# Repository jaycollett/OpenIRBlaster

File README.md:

# OpenIRBlaster

An open-source IR receiver and transmitter for Home Assistant. Custom PCB, 3D-printed case, ESPHome firmware, about $22 to $25 in parts.

[![GitHub Release][releases-shield]][releases]
[![License][license-shield]](LICENSE)
[![hacs][hacsbadge]][hacs]

📖 **[Read the full story and build guide on my blog](https://www.jaycollett.com/2026/02/openirblaster-finally-truly-simple-ir-control-for-home-assistant/)**

## The integration is deprecated. The hardware is not.

Home Assistant 2026.4 added a built-in `infrared` entity platform, and [HAIR](https://github.com/DAB-LABS/HAIR) builds a full IR code manager on top of it: a live signal sniffer, protocol decoding, climate state matrices, and import from SmartIR, Flipper Zero, LIRC and Girr. It does everything this integration does and a great deal more, and it is in the HACS default store.

So this integration is winding down. It still works, it is not going to break tomorrow, and nothing is being deleted in this release. It will not gain new features.

The hardware is unaffected and is where this project continues. OpenIRBlaster is a board, a case, a bill of materials and a firmware image, none of which HAIR provides.

**If you are already using this integration:** move your codes across before you delete its storage file. From version 1.3.2, removing the integration leaves that file in place. Version 1.3.1 and earlier deleted it along with the integration, so on those versions update or move your codes first. Your stored codes hold the carrier frequency measured when each was learned, and the new infrared platform does not report one, so anything re-learned later comes back at the 38 kHz default. See [Moving your codes to HAIR](#moving-your-codes-to-hair). Nothing is deleted and your setup keeps working while you check the result.

**If you are new here:** build the hardware, flash it, and use it with HAIR.

## What it is

A dedicated ESP8266 board built around IR, rather than a general-purpose dev board with an LED soldered on.

Transistor-driven IR LEDs (eight of them, 39 ohm limiting resistors, IRLML6344 MOSFET) give strong output and 360 degree coverage, so it works across a room rather than only when pointed at the target. A TSOP38238 receiver handles learning. The ESPHome firmware ships with `dashboard_import`, so the ESPHome dashboard can adopt the device with one click.

Everything needed to build one is in [`hardware/`](hardware/): schematic and board layout, the bill of materials, STLs for the case, the firmware source and a prebuilt binary.

## Requirements

- Home Assistant 2024.12 or newer for this integration.
- For HAIR, check its own requirements. Native IR capture and plucking need Home Assistant 2026.6 or newer, because that is the release where the infrared receiver API landed. 2026.9 or newer is the safer floor.
- An OpenIRBlaster board, or other ESPHome hardware with an IR receiver and transmitter.

See the [Hardware Overview](docs/hardware-overview.md) for the build.

## Moving your codes to HAIR

### Do this before you delete anything

Every code you learned here carries the carrier frequency measured when it was captured. Home Assistant's infrared platform does not report a carrier, so a code you learn again afterwards comes back at the 38 kHz default.

Most remotes are 38 kHz and would not notice. A device running at 36 or 40 kHz would, and for those the difference is the code working or not working. That measured value exists in one place only, this integration's storage file, and re-learning cannot bring it back.

Both routes below preserve it. Take one of them before you delete `.storage/openirblaster_<entry_id>`.

From version 1.3.2, removing the integration in Home Assistant keeps that file, so your codes are still on disk afterwards and the command-line export below can convert them. Version 1.3.1 and earlier deleted the file when you deleted the integration entry, so if you are on one of those versions, update or export first.

If you remove a blaster and add it again, Home Assistant gives it a new entry ID and a new, empty storage file. The old file stays next to it with your codes in it. Once those codes are safely in HAIR you can delete the old file by hand.

### Pluck from HAIR (recommended)

HAIR pulls the codes out of this integration directly. No files to move, no remote to point at anything, and no infrared is broadcast while it happens.

1. Install HAIR from HACS and set it up.
2. Open HAIR, go to the **Plucker** tab, and add OpenIRBlaster as a blaster.
3. Pluck your codes by name.

This works because the integration implements HAIR's pluckable contract. See [Plucking codes into HAIR](docs/pluckable.md) for what that means and how it works.

### Export to a file

If you would rather move files yourself, or HAIR is not installed yet.

From the UI, while this integration is still installed:

1. Go to **Developer Tools** -> **Actions**.
2. Choose **OpenIRBlaster: Export codes to HAIR**.
3. Pick your device, and optionally choose how to split the codes into files.
4. Run it.

Files land in `hair/wigs/` in your Home Assistant config directory, which is where HAIR looks.

HAIR treats one file as one remote, so the **Split into** option matters if your library covers several devices. Splitting by tag or by the first word of each code name gives you one remote per device instead of one long list. You can re-split inside HAIR later either way.

From the command line, which also works after you have removed the integration (on 1.3.2 or later, where removal keeps the file):

```bash
python3 tools/openirblaster_to_wig.py ~/.homeassistant/.storage/openirblaster_<entry_id>
```

The file name has no extension, and there is one per blaster, so `ls ~/.homeassistant/.storage/openirblaster_*` shows you what to pass.

Run `--help` for output directory and grouping options. It needs nothing but Python 3.12 or newer and never writes to the file it reads. `custom_components/openirblaster/wig_export.py` is the whole implementation in one file with no imports from anything else, so you can copy that single file somewhere and run it if the repository is not handy.

### After moving

Check the codes work in HAIR before removing anything here. If a code did not convert, or carried tags or notes, the file export writes `openirblaster-export-receipt.txt` next to the wigs listing what was dropped and why. Tags and notes have no equivalent in HAIR's format, so they are reported rather than silently merged.

Keep your `.storage` file until you are satisfied. Removing the integration does not touch it, so when you no longer need it, delete it by hand.

## Installation

### HACS

1. Open HACS.
2. Click **Integrations**.
3. Click **+ Explore & Download Repositories**.
4. Search for "OpenIRBlaster".
5. Click **Download**.
6. Restart Home Assistant.
7. Go to **Settings** → **Devices & Services** → **Add Integration** and search for "OpenIRBlaster".

### Manual

1. Download the [latest release](https://github.com/jaycollett/OpenIRBlaster/releases).
2. Copy `custom_components/openirblaster` into your Home Assistant `custom_components` directory.
3. Restart Home Assistant.
4. Add the integration from **Settings** → **Devices & Services**.

## Using the integration

### Learn a code

1. Find the **Code Name** text field in your device's entity list.
2. Enter a name, for example "TV Power".
3. Press **Learn IR Code**.
4. Within 30 seconds, point your remote at the receiver and press the button.
5. A new button entity appears with that name.

### Manage codes

Rename by calling `openirblaster.rename_code` with the code's `id` and a `new_name`. The button updates immediately and its entity ID does not change, so automations keep working.

Delete from **Settings** → **Devices & Services** → **OpenIRBlaster** → **Configure** → **Manage IR Codes**. Deletion is always select-then-confirm.

Codes can also be saved, sent, renamed and deleted from scripts. See the [Home Assistant Integration](docs/home-assistant-integration.md) docs for the full service reference.

### Use in automations

```yaml
automation:
  - alias: "Turn off TV at bedtime"
    trigger:
      - platform: time
        at: "23:00:00"
    action:
      - service: button.press
        target:
          entity_id: button.openirblaster_tv_power
```

## Compatibility

The integration finds devices by ESPHome project name, looking for firmware that declares `project.name: "jaycollett.openirblaster"`. If you are building your own hardware, include that identifier in your ESPHome YAML or fork the integration.

### Third-party devices

Community members have run OpenIRBlaster on hardware it was not designed for. See [`docs/third-party-devices/`](docs/third-party-devices/):

- [Tuya IR Blasters](docs/third-party-devices/tuya-ir-blasters.md), covering S06, S18 and similar Tuya-branded repeaters

[PRs adding a guide are welcome](docs/third-party-devices/README.md#contributing-a-new-device-guide).

## Documentation

Full documentation lives in [`docs/`](docs/README.md):

- [Hardware Overview](docs/hardware-overview.md), schematic, components and build guide
- [Firmware & ESPHome](docs/firmware-and-esphome.md), flashing and configuration
- [Home Assistant Integration](docs/home-assistant-integration.md), setup, entities, services and automation examples
- [Plucking codes into HAIR](docs/pluckable.md), how HAIR pulls codes out of this integration
- [Storage Format & Manual Editing](docs/storage-format.md), on-disk schema and hand-edit procedure
- [Troubleshooting](docs/troubleshooting.md), common issues and solutions

## Development

- [`TESTING.md`](TESTING.md), testing instructions
- [`hardware/`](hardware/), hardware design files

### ESPHome firmware

The firmware configuration is at [`hardware/firmware/factory_flash.yaml`](hardware/firmware/factory_flash.yaml). To contribute changes, modify the YAML, test on your own device, and keep event names, service calls and entity IDs compatible with the integration. See the [Firmware & ESPHome](docs/firmware-and-esphome.md) docs.

### Integration

```bash
git clone https://github.com/jaycollett/OpenIRBlaster.git
cd OpenIRBlaster
python3 -m venv venv
source venv/bin/activate
pip install -r requirements_dev.txt

pytest
```

## Support

- [Report bugs or request features](https://github.com/jaycollett/OpenIRBlaster/issues)
- [Project documentation](docs/README.md)

## License

MIT. See [LICENSE](LICENSE).

## Acknowledgments

Built for the Home Assistant community. Thanks to the ESPHome project for the firmware platform, to the Home Assistant community, and to [DAB-LABS](https://github.com/DAB-LABS/HAIR) for building the IR code manager this project no longer needs to.

### Transparency note: AI-assisted development

The Home Assistant integration for this project was developed with assistance from [Claude Code](https://claude.ai/code), Anthropic's AI coding assistant. AI-assisted development is a powerful tool when used responsibly by engineers who understand the code being generated, validate its correctness, and take ownership of the final result. I reviewed, tested, and take full responsibility for all code in this repository. AI assistance accelerated development but doesn't replace engineering judgment, thorough testing, or understanding of the underlying systems.

---

[releases-shield]: https://img.shields.io/github/v/release/jaycollett/OpenIRBlaster
[releases]: https://github.com/jaycollett/OpenIRBlaster/releases
[license-shield]: https://img.shields.io/github/license/jaycollett/OpenIRBlaster.svg
[hacs]: https://github.com/hacs/integration
[hacsbadge]: https://img.shields.io/badge/HACS-Default-orange.svg

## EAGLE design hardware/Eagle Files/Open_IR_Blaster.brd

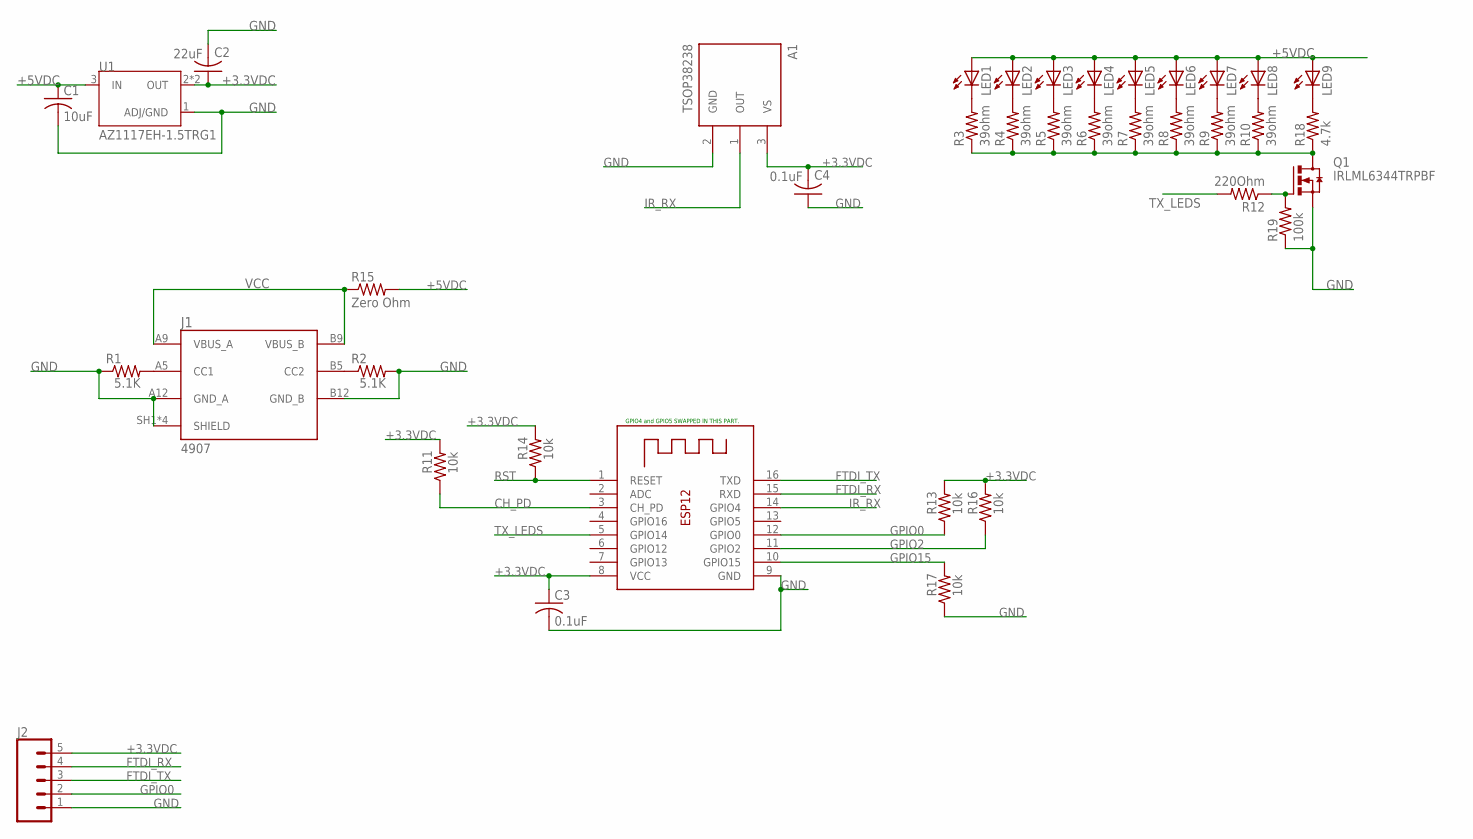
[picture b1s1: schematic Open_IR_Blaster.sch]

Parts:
A1: TSOP38238; XDCR_TSOP38238
C1: 10uF; C0805
C2: 22uF; C0805
C3, C4: 0.1uF; C0805
J1: 4907; ADAFRUIT_4907
J2: CONN_05PTH_LONGPADS; 1X05_LONGPADS
LED1, LED2, LED3, LED4, LED5, LED6, LED7, LED8: LED5MM
LED9: LEDCHIP-LED0603; CHIP-LED0603
Q1: IRLML6344TRPBF; SOT23
R1, R2: 5.1K; M0805
R3, R4, R5, R6, R7, R8, R9, R10: 39ohm; R1210
R11, R13, R14, R16, R17: 10k; M0805
R12: 220Ohm; M0805
R15: Zero Ohm; R1210
R18: 4.7k; R0603
R19: 100k; R0603
U1: AZ1117EH-1.5TRG1; SOT230P700X180-4N
X1: ESP-12

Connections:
+3.3VDC: A1.3 (VS), C2.1, C3.1, C4.2, J2.5, R11.2, R13.2, R14.2, R16.2, U1.2 (OUT), U1.4 (OUT), X1.8 (VCC)
+5VDC: C1.1, LED1.A, LED2.A, LED3.A, LED4.A, LED5.A, LED6.A, LED7.A, LED8.A, LED9.A, R15.2, U1.3 (IN)
CH_PD: R11.1, X1.3 (CH_PD)
FTDI_RX: J2.4, X1.15 (RXD)
FTDI_TX: J2.3, X1.16 (TXD)
GND: A1.2 (GND), C1.2, C2.2, C3.2, C4.1, J1.A12 (GND_A), J1.B12 (GND_B), J1.SH1 (SHIELD), J1.SH2 (SHIELD), J1.SH3 (SHIELD), J1.SH4 (SHIELD), J2.1, Q1.2 (S), R1.1, R2.2, R17.1, R19.1, U1.1 (ADJ/GND), X1.9 (GND)
GPIO0: J2.2, R13.1, X1.12 (GPIO0)
GPIO2: R16.1, X1.11 (GPIO2)
GPIO15: R17.2, X1.10 (GPIO15)
IR_RX: A1.1 (OUT), X1.14 (GPIO4)
unnamed: LED1.K (C), R3.2
unnamed: LED2.K (C), R4.2
unnamed: LED3.K (C), R5.2
unnamed: LED4.K (C), R6.2
unnamed: LED5.K (C), R7.2
unnamed: LED6.K (C), R8.2
unnamed: LED7.K (C), R9.2
unnamed: LED8.K (C), R10.2
unnamed: Q1.3 (D), R3.1, R4.1, R5.1, R6.1, R7.1, R8.1, R9.1, R10.1, R18.1
unnamed: J1.A5 (CC1), R1.2
unnamed: J1.B5 (CC2), R2.1
unnamed: Q1.1 (G), R12.1, R19.2
unnamed: LED9.C, R18.2
RST: R14.1, X1.1 (RESET)
TX_LEDS: R12.2, X1.5 (GPIO14)
VCC: J1.A9 (VBUS_A), J1.B9 (VBUS_B), R15.1

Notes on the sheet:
GPIO4 and GPIO5 SWAPPED IN THIS PART.

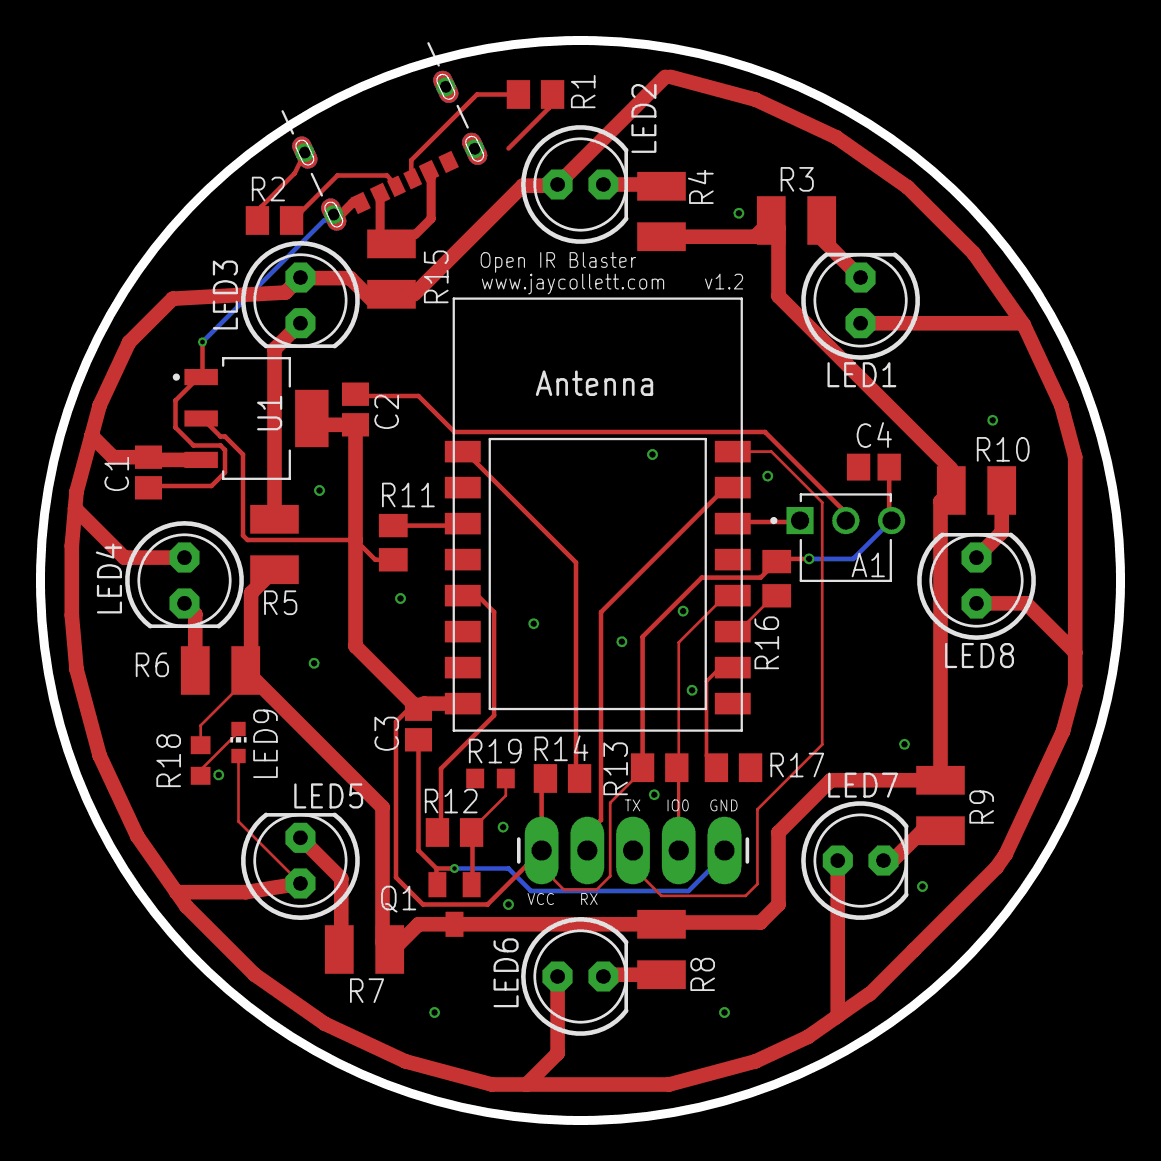
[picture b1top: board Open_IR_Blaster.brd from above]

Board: 2 copper layers, 60.0 x 60.0 mm, 38 parts (0 on the bottom side), 26 nets.

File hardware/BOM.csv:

Component Type,Value,Designator,Footprint,Part Details
SMT Capacitor,0.1uF,X1 C3 C4,C0805,
SMT Resistor,5.1K,R1 R2,M0805,RC0805FR-075K1L
SMT Resistor,10k,R11 R13 R14 R16 R17,M0805,
SMT Capacitor,10uF,C1,C0805,GRM21BR61C106KE15K
SMT Capacitor,22uF,C2,C0805,GRM21BR61A226ME51K
SMT Resistor,39ohm,R3 R4 R5 R6 R7 R8 R9 R10,R1210,RC1210FR-0739RL
SMT Resistor,220Ohm,R12,M0805,RC0805FR-07220RL
Connector,USB Power Port,J1,ADAFRUIT_4907,4907
Voltage Regulator,3.3V,U1,SOT230P700X180-4N,AZ1117IH-3.3TRG1
MOSFET,IRLML6344TRPBF,Q1,SOT23,IRLML6344TRPBF
SMT Resistor,Zero Ohm,R15,R1210,RMCF1210ZT0R00
MCU,ESP8266,MCU,ESP-12F,ESP-12F
TH 5MM LED,IR (940nm),LEDX,TH,IR333-A
IR Receiver,38kHz,A1,TH,TSOP38238

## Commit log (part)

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2025-01-16 Initial commit, v1.1
2025-01-17 Adds initial version of enclosure.
2026-01-12 Initial commit: OpenIRBlaster Home Assistant Integration
    This integration provides comprehensive IR code learning, storage, and
    transmission capabilities for ESPHome-based IR blaster devices.
    Features:
    - Learn IR codes from any remote control
    - Store codes with names, tags, and notes
    - Button entities for easy code transmission
2026-01-13 Add integration assets and localization strings
    - Add assets/logo.png for branding
    - Add strings.json with localization for config flow, options, and services
2026-01-13 Add hardware design files and documentation
    - Add 3D printer files: Bottom.stl and Top.stl for enclosure
    - Add Eagle PCB design files: schematic and board layout
    - Add Bill of Materials (BOM.csv)
    - Add LICENSE file
2026-01-13 Move firmware files into hardware/firmware/ subfolder
    Organize firmware files in their own subfolder for better structure:
    - hardware/firmware/factory_config.yaml
    - hardware/firmware/factory_firmware.bin
2026-01-13 Fix critical firmware stability issues
    Config changes:
    - Change time platform from homeassistant to sntp (fixes Exception 28 crash on boot)
    - Enable API watchdog: reboot_timeout 0s -> 5min (auto-recovery from connection issues)
    - Use UTC timezone for SNTP (works without HA connection)
    Binary update:
    - Update factory_firmware.bin with latest build incorporating these fixes
2026-01-13 Revert firmware configuration changes
    Revert back to original settings:
    - reboot_timeout: 0s (from 15min)
    - time platform: homeassistant (from sntp)
    Device works after automatic reboot, will address crashes in future update.
2026-01-13 Revert time platform back to homeassistant
    Only reboot_timeout at 0s remains reverted. Time platform back to original.
2026-01-13 Fix C++ preprocessor directive errors in comments
    Change all comments inside action blocks to start with lowercase to prevent
    C++ preprocessor from interpreting them as directives like #Disable, #Preferred, etc.
    Fixed comments:
    - Line 135: Preferred -> preferred
    - Line 167: Optional -> optional
    - Line 197: Disable -> disable
2026-01-13 Restore comments that weren't causing compilation errors
    Only the comment before switch.turn_off was causing the C++ preprocessor error.
    Restored the other two comments:
    - Comment before homeassistant.event action
    - Comment before debug lambda action
2026-01-13 Add delete button for learned IR codes and fix sensor persistence
    - Add DeleteCodeButton entity for each learned code providing one-click deletion
    - Fix deletion workflow to use entity registry removal instead of integration reload
    - Persist sensor data (name, timestamp, pulse count) in hass.data across reloads
    - Update delete_code service to auto-detect config_entry_id when not provided
    - Initialize sensor persistence fields in __init__.py
    This improves UX by allowing users to delete codes with a simple button press
2026-01-13 Add debug logging to ESPHome firmware and integration logo
    - Add logging for send_ir_raw service calls with carrier frequency and code length
    - Add logging for IR learning mode enable/disable events
    - Add logging when IR codes are received during learning mode
    - Add logo.png for integration icon display in Home Assistant
2026-01-13 Fixes the issue with mac suffix after HA adoption.
2026-01-14 Implement two-device architecture and improve learning workflow
    Changes:
    - Split into main device (IR code buttons) and controls device (learning/management UI)
    - Add duplicate code name detection with user notification
    - Disable delete buttons by default for safety
    - Clear pending code on duplicate name to prevent double notifications
    - Move Learn, Send Last, Delete buttons and Code Name text input to controls device
2026-01-19 Add factory_flash.yaml for initial device flashing
    Two-file firmware architecture:
    - factory_flash.yaml: For factory flashing, uses name_add_mac_suffix: true
    so devices advertise with unique names (e.g., openirblaster-64c999)
    - factory_config.yaml: Pulled from GitHub on ESPHome adoption, uses
    name_add_mac_suffix: false since ESPHome captures the full unique name
    This prevents the double MAC suffix issue when devices are adopted.
2026-01-19 Remove binary firmware files from repo
    Binary .bin files are build artifacts and shouldn't be tracked in git.
2026-01-20 Prepare integration for HACS publishing
    Major changes:
    - Add HACS configuration (hacs.json)
    - Fix device discovery fallback for empty ESPHome identifiers
    - Add helpers.py for ESPHome service discovery
    - Improve config flow robustness for multi-device support
    - Update README with new firmware installation instructions
2026-01-20 Fix Hassfest validation errors
    - Remove homeassistant key from manifest (not needed for custom integrations)
    - Remove exceptions section from strings.json (not supported by Hassfest)
2026-01-20 Add diagnostics support
2026-01-20 Restore last learned sensors across restarts
2026-01-20 Fix options flow init
2026-01-20 Harden options flow config entry handling
2026-01-20 Show device name in code delete list
2026-01-20 Remove per-code delete button entities
2026-01-22 Adds indicator LED to board and pulldown for MOSFET (not required).
2026-01-31 Add schematic PNG to hardware files
2026-01-31 Revert "Simplify README with links to blog post and Wiki"
    This reverts commit d84106a8a487668177ec256ca1f2f4b376208cdb.
2026-01-31 Use first-person in AI acknowledgment
2026-01-31 Remove CLAUDE.md link from README
2026-01-31 Remove local utility scripts from repo and add to gitignore
2026-01-31 Align README with project scope and blog content
2026-01-31 Trigger contributor cache refresh
2026-01-31 Add stale and lock bots for issue management
    - stale.yml: Marks issues/PRs stale after 60 days, closes after 7-14 more
    - lock.yml: Locks closed issues after 30 days, PRs after 7 days
2026-02-04 Add link to blog post in README
    Added a prominent link to the detailed blog post with the full story
    and build guide for OpenIRBlaster.
2026-02-04 Fix dashboard_import URL to use master branch
2026-02-05 v1.0.3: Support carrier frequencies from 30kHz to 56kHz
    Aligns validation range with TSOP382xx drop-in receiver options.
    Transmission at these frequencies was already supported; this
    update properly validates the full range for the send_code service.
    Closes #2
2026-02-05 Add CI/CD workflows and branch protection
    - Add ci.yml: runs pytest, ruff linting, and version check on PRs
    - Add release.yml: auto-creates GitHub releases when PRs merge to master
    - Fix validate.yaml: scope triggers to master branch only (prevents doubled checks)
    - Add mock esphome integration for tests (satisfies dependency requirement)
    - Fix test_config_flow.py: update tests for discovery-based config flow
    - Fix test_learning.py: fix async clear_pending test, add persistent_notification mock
2026-04-02 Simplify CLAUDE.md to essential information
2026-04-23 Default Code Name field to blank instead of placeholder text
    Closes #6.
    Previously the Code Name text entity initialized to the literal string
    "Enter Code Name" and was reset to the same value after each save,
    which meant users had to clear the field before typing. Defaulting the
    entity to an empty string lets HA render the input as visually empty
    while the entity's native_min=0 keeps empty values valid.
2026-04-23 Clean up CI: remove dead test mock, bump GitHub Actions to Node 24
    - Delete unused tests/components/esphome mock package. The current
    conftest.py mocks ESPHome via loader.async_get_integration patching
    rather than a custom_components-style fixture, so this directory was
    dead code. Hassfest was scanning it as if we were Home Assistant
    core, which produced two spurious warnings on every Validate run:
    'Domain collides with built-in core integration' (collided with the
2026-04-24 Fix LearnButton callback registration leak
    LearnButton was registering _handle_learning_complete on every press but
    only unregistering inside _async_save_learned_code's finally block. If a
    press ended via timeout, cancel, or start-failure the callback stayed
    registered. The next press appended another copy of the same bound
    method, and when STATE_RECEIVED eventually arrived the save handler
    fired multiple times concurrently.
2026-04-24 Guard learning-session race between validation-failure and valid capture
    Validation-failure branches in both capture handlers previously scheduled
    _async_cancel asynchronously without flipping _capture_finalized. Between
    the cancel being scheduled and the cancel task actually running, the
    other capture path (event vs text_sensor) could slip a valid payload
    through the STATE_ARMED + not finalized guard and commit a capture that
    the pending cancel would then clobber.
2026-04-24 Expand learning test coverage for resolver, race guard, and MAC back-fill
    Adds tests that QA flagged as missing or weak in the issue #8 review:
    - Strategy 1 resolver: verify device-registry-by-MAC lookup succeeds
    even when the Strategy 2 slug heuristic would miss (custom ESPHome
    entity naming). Proves Strategy 1 works independently of Strategy 2.
    - Resolver returns None: confirm graceful degradation - event path
    stays subscribed, state_listener is None, warning is logged.
2026-04-24 Bump version to 1.0.6
    Fixes IR learning that broke after HA 2026.4 + ESPHome 2026.4 when
    transient native-API socket disconnects caused the `esphome.openirblaster_learned`
    event to be lost. The integration now subscribes to the firmware's
    `last_ir_raw_snippet` text_sensor as a secondary capture path, which
    survives reconnects, and dedups against the event path.
    Also fixes a callback-registration leak in the Learn button that could
2026-05-20 Fix dangling-pointer MAC and rebuild dropped-event recovery (v1.0.7 / firmware 0.5.0)
    Two bundled fixes for issue #11 and a long-standing latent failure in the
    text_sensor fallback path:
    1. Firmware MAC field was a dangling pointer.
    The on_raw lambda returned WiFi.macAddress().c_str(), which is a pointer
    into an Arduino String temporary. The String dies at the end of the
    lambda's return statement, so by the time ESPHome's templating wrapper
2026-06-12 Replace entry reloads with dynamic entities, add event platform and learn_cancel, fix QA findings
    Architecture:
    - Code add/delete/rename now updates entities live via dispatcher signals
    instead of reloading the config entry; learning sessions survive saves
    - Management entities use entity categories on the main device; the virtual
    "Controls" device is removed with an idempotent registry migration that
    preserves user customizations (covers both MAC and device_id identifiers)
2026-06-12 Sweep orphaned entity registry entries at setup (v1.2.1)
    Old integration versions left stale entity registry entries behind,
    most notably the per-code delete buttons removed in January without
    registry cleanup. Setup now removes any registry entry owned by the
    integration whose unique_id is not in the authoritative set (static
    entities plus one button per stored code), logging each removal. The
    sweep is idempotent, scoped to the config entry and platform, and

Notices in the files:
parts and their libraries:
SparkFun-Connectors: Licensing: Creative Commons ShareAlike 4.0 International - https://creativecommons.org/licenses/by-sa/4.0
